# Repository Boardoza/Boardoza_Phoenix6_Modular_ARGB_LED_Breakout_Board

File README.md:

# Boardoza Phoenix6 Breakout Board

The **Boardoza Phoenix6** is a compact, circular **addressable RGB lighting breakout board** featuring **six RGB LEDs** arranged in a ring configuration. Each LED is individually addressable, allowing precise control over color and brightness for dynamic lighting effects.

With its modular and chainable design, multiple B-Phoenix6-BRK boards can be connected to create custom lighting patterns, symbols, or visual indicators. Supporting **both 3.3V and 5V logic levels,** the board is fully compatible with common microcontrollers and development platforms. This makes it a reliable choice for DIY electronics, decorative lighting, wearables, and interactive display applications, whether for prototyping or finished projects.

## [Click here to purchase!](https://www.ozdisan.com/ureticiler/boardoza)
| Front Side | Back Side |
|:---:|:---:|
|  |  |

---

## Key Features

- **6x Addressable RGB LEDs:** Each LED can be individually controlled for color and brightness, enabling dynamic lighting effects and smooth animations.  
- **Modular Daisy-Chain Design:** Multiple boards can be connected to build custom lighting patterns and effects.
- **Dual Voltage Compatibility:** Operates with both 3.3 V and 5 V power supplies.
- **Logic Level Support:** Fully compatible with **TTL and CMOS** logic systems.
- **Flexible Connection Options:** Includes both **SMD and Through-Hole (THR) pads** for input and output connections.
- **Creative Application Ready:** Suitable for interactive lighting, wearables, decorative projects, and visual indicators.

---

## Technical Specifications

**Model:** Phoenix6  
**Manufacturer:** Boardoza  
**Function:** Individually Addressable RGB Lighting  
**Input Voltage:** 3.3 V / 5 V  
**LED Model:** T3A33BRG-H9C0002X1U1930   
**Number of LEDs:** 6  
**LED Type:** Individually addressable RGB LEDs  
**Logic Compatibility:** TTL / CMOS  
**Data Interface:** Serial Data & Clock (DIN / CIN / DOUT / COUT)  
**Daisy-Chain Support:** Yes  
**Operating Temperature:** -40 °C to +85 °C  
**Board Dimensions:** 31.79 mm × 31.71 mm  

---

## Board Pinout

### ( J1 ) Output Connector

| Pin Number | Pin Name | Description |
| :---: | :---: | --- |
| 1 | DOUT | Serial data output |
| 2 | COUT | Clock output |

### ( J2 ) Input Connector

| Pin Number | Pin Name | Description |
| :---: | :---: | --- |
| 1 | DIN | Serial data input |
| 2 | CIN | Clock input |

### ( J3 ) Power Connector

| Pin Number | Pin Name | Description |
| :---: | :---: | --- |
| 1 | VCC | Power supply (3.3V / 5V) |
| 2 | GND | Ground |

### ( J4 ) Power Connector

| Pin Number | Pin Name | Description |
| :---: | :---: | --- |
| 1 | VCC | Power supply (3.3V / 5V) |
| 2 | GND | Ground |

---

## Board Dimensions

---

## Step Files

[Boardoza Phoenix6.step](./assets/Phoenix6%20Step.step)

---

## Datasheet

[T3A33BRG Datasheet](./assets/Phoenix6%20Datasheet.pdf)

---

## Version History

- **V1.0.0** – Initial Release

---

## Support

- For questions or technical support, please contact **support@boardoza.com**

---

## **License**

This repository contains both hardware and software components:

### **Hardware Design**

[![CC BY-SA 4.0][cc-by-sa-shield]][cc-by-sa]

All hardware design files are licensed under [Creative Commons Attribution-ShareAlike 4.0 International License][cc-by-sa].

[cc-by-sa]: http://creativecommons.org/licenses/by-sa/4.0/
[cc-by-sa-shield]: https://img.shields.io/badge/License-CC%20BY--SA%204.0-lightgrey.svg

### **Software/Firmware**

[![BSD-3-Clause][bsd-shield]][bsd]

All software and firmware are licensed under [BSD 3-Clause License][bsd].

[bsd]: https://opensource.org/licenses/BSD-3-Clause
[bsd-shield]: https://img.shields.io/badge/License-BSD%203--Clause-blue.svg

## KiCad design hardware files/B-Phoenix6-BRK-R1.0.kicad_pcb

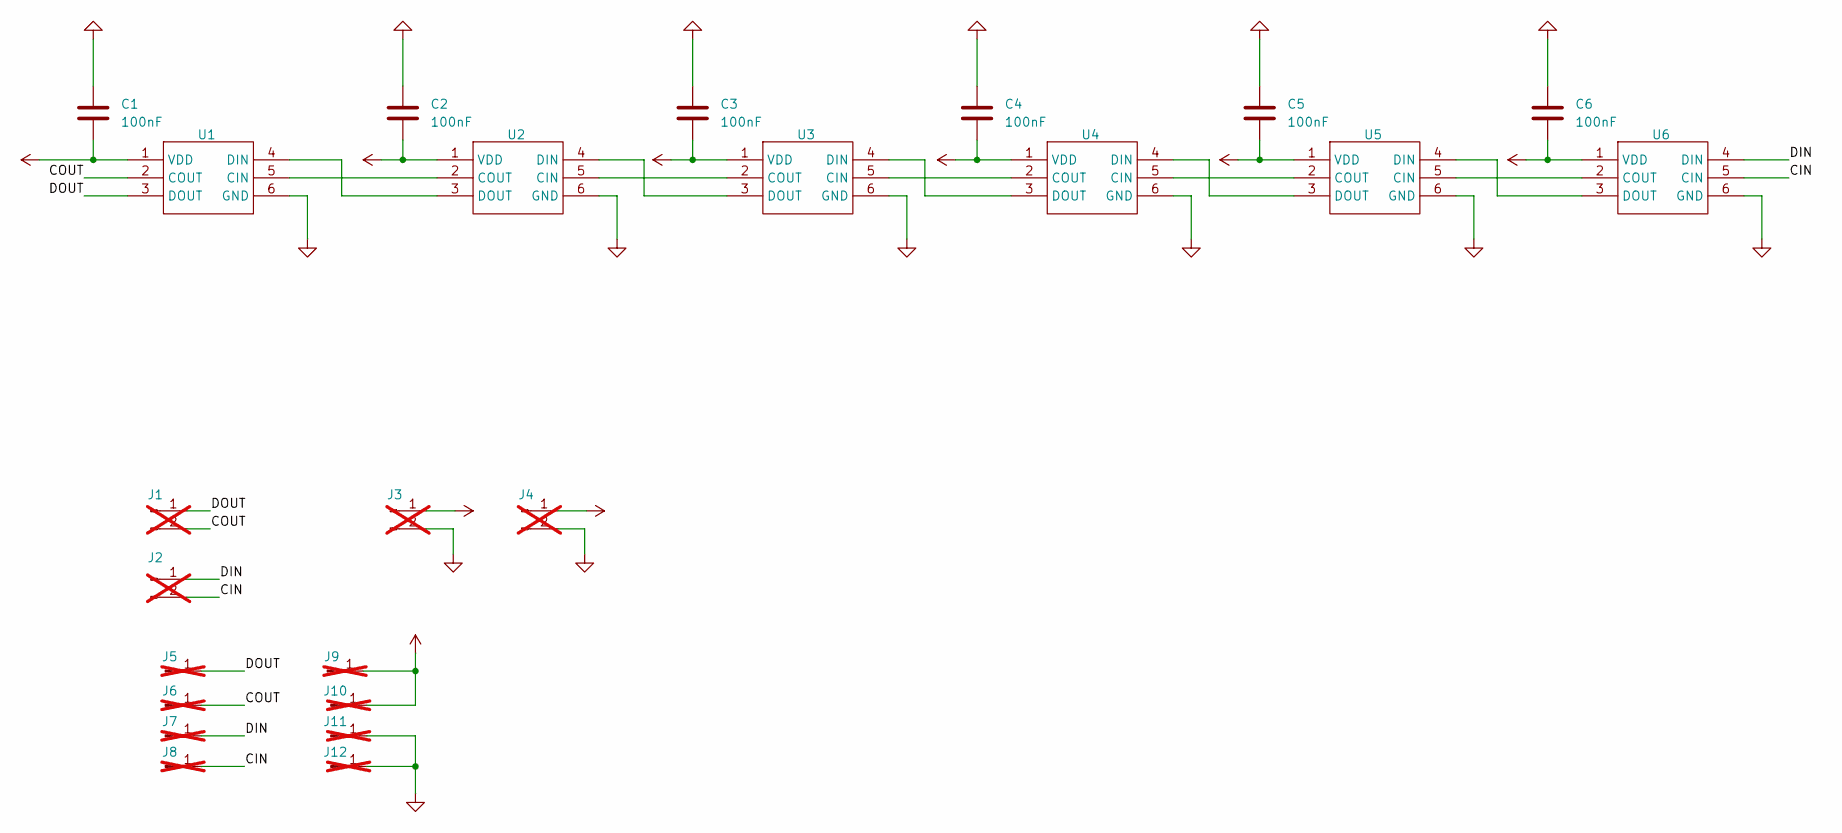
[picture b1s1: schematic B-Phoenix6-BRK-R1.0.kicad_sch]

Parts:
C1, C2, C3, C4, C5, C6: 100nF; C_0603_1608Metric; MPN MCF03KTB500104
J1, J2, J3, J4: Conn_01x02_Pin; PinSocket_1x02_P2.54mm_Vertical; not fitted
J5, J6, J7, J8, J9, J10, J11, J12: Conn_01x01_Pin; SolderWirePad_1x01_SMD_1x2mm; not fitted
U1, U2, U3, U4, U5, U6: T3A33BRG-H9C0002X1U1930_HVK; MPN T3A33BRG-H9C0002X1U1930

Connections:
/CIN: J2.2, J8.1, U6.5 (CIN)
/COUT: J1.2, J6.1, U1.2 (COUT)
/DIN: J2.1, J7.1, U6.4 (DIN)
/DOUT: J1.1, J5.1, U1.3 (DOUT)
GND: C1.1, C2.1, C3.1, C4.1, C5.1, C6.1, J3.2, J4.2, J11.1, J12.1, U1.6 (GND), U2.6 (GND), U3.6 (GND), U4.6 (GND), U5.6 (GND), U6.6 (GND)
unnamed: U1.5 (CIN), U2.2 (COUT)
unnamed: U1.4 (DIN), U2.3 (DOUT)
unnamed: U2.5 (CIN), U3.2 (COUT)
unnamed: U2.4 (DIN), U3.3 (DOUT)
unnamed: U3.5 (CIN), U4.2 (COUT)
unnamed: U3.4 (DIN), U4.3 (DOUT)
unnamed: U4.5 (CIN), U5.2 (COUT)
unnamed: U4.4 (DIN), U5.3 (DOUT)
unnamed: U5.5 (CIN), U6.2 (COUT)
unnamed: U5.4 (DIN), U6.3 (DOUT)
VCC: C1.2, C2.2, C3.2, C4.2, C5.2, C6.2, J3.1, J4.1, J9.1, J10.1, U1.1 (VDD), U2.1 (VDD), U3.1 (VDD), U4.1 (VDD), U5.1 (VDD), U6.1 (VDD)

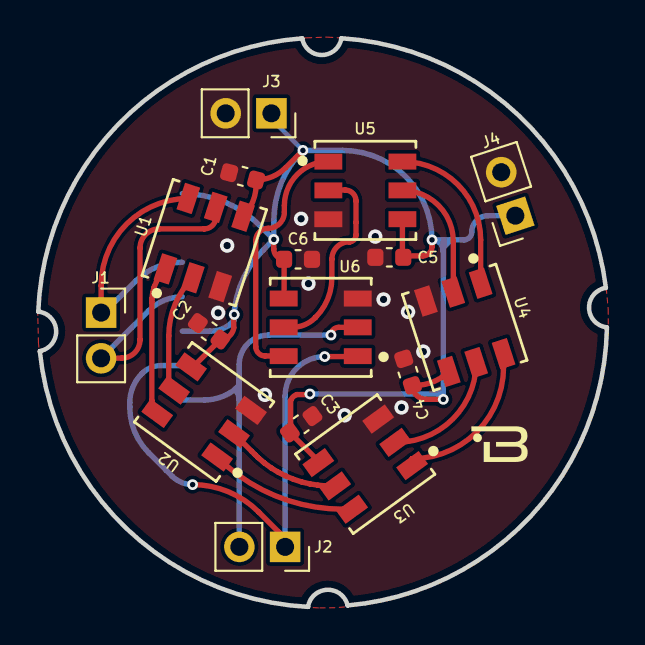
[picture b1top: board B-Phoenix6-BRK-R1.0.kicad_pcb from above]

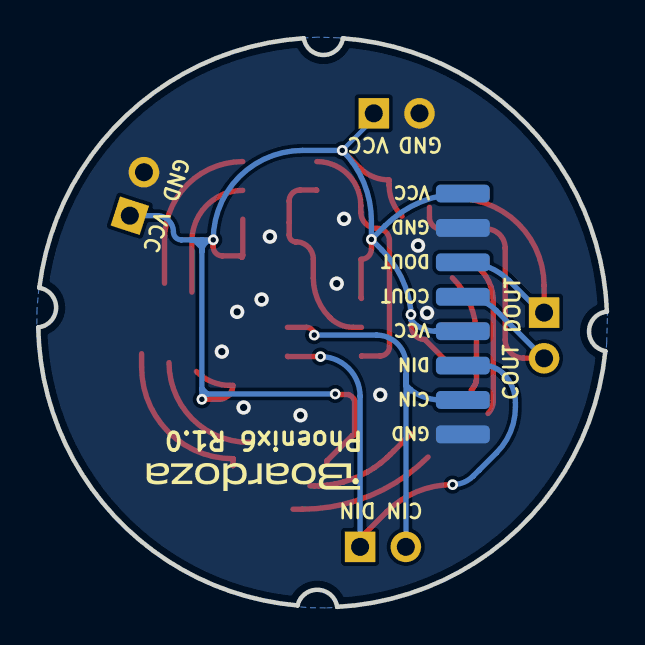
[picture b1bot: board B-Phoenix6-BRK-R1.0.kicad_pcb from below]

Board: 2 copper layers, 31.6 x 31.6 mm, 24 parts (8 on the bottom side), 16 nets.

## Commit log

2026-04-28 Fix hueOffset declaration formatting
2026-04-28 Fixed comment lines
